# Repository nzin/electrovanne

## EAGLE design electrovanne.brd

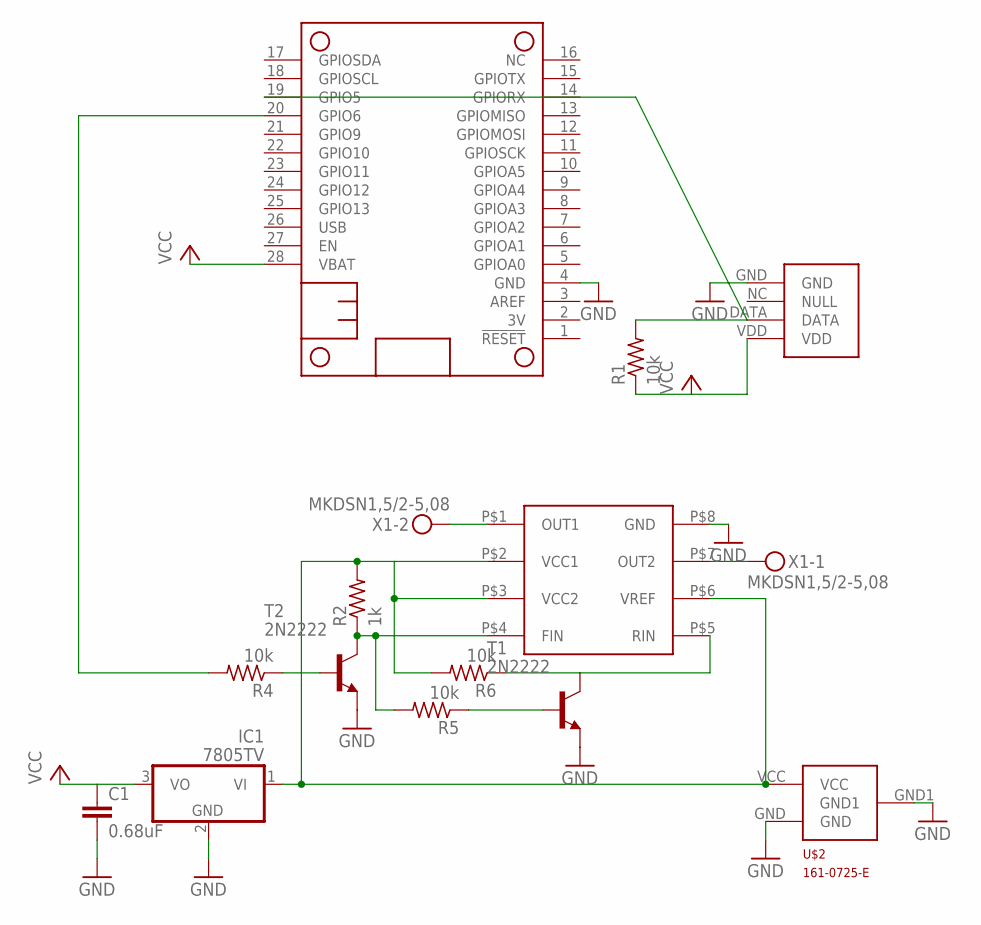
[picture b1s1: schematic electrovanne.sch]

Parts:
C1: 0.68uF; 0603-CAP
IC1: 7805TV; TO220V
MS1: FEATHERWING_NODIM; FEATHERWING_DIM
R1, R4, R5, R6: 10k; R0603
R2: 1k; R0603
T1, T2: 2N2222; TO18
U$1: DHT22
U$2: 161-0725-E
U$4: 755-BD6211F-E2; 755-BD6211F-E2_DIM
X1: MKDSN1,5/2-5,08

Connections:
GND: C1.2, IC1.2 (GND), MS1.4 (GND), T1.1 (E), T2.1 (E), U$1.GND, U$2.GND, U$2.GND1, U$4.P$8 (GND)
unnamed: IC1.1 (VI), R2.2, R6.2, U$2.VCC, U$4.P$2 (VCC1), U$4.P$3 (VCC2), U$4.P$6 (VREF)
unnamed: R5.1, T1.2 (B)
unnamed: MS1.19 (GPIO5), R1.2, U$1.DATA
unnamed: U$4.P$1 (OUT1), X1.2
unnamed: U$4.P$7 (OUT2), X1.1
unnamed: MS1.20 (GPIO6), R4.2
unnamed: R2.1, R5.2, T2.3 (C), U$4.P$4 (FIN)
unnamed: R4.1, T2.2 (B)
unnamed: R6.1, T1.3 (C), U$4.P$5 (RIN)
VCC: C1.1, IC1.3 (VO), MS1.28 (VBAT), R1.1, U$1.VDD

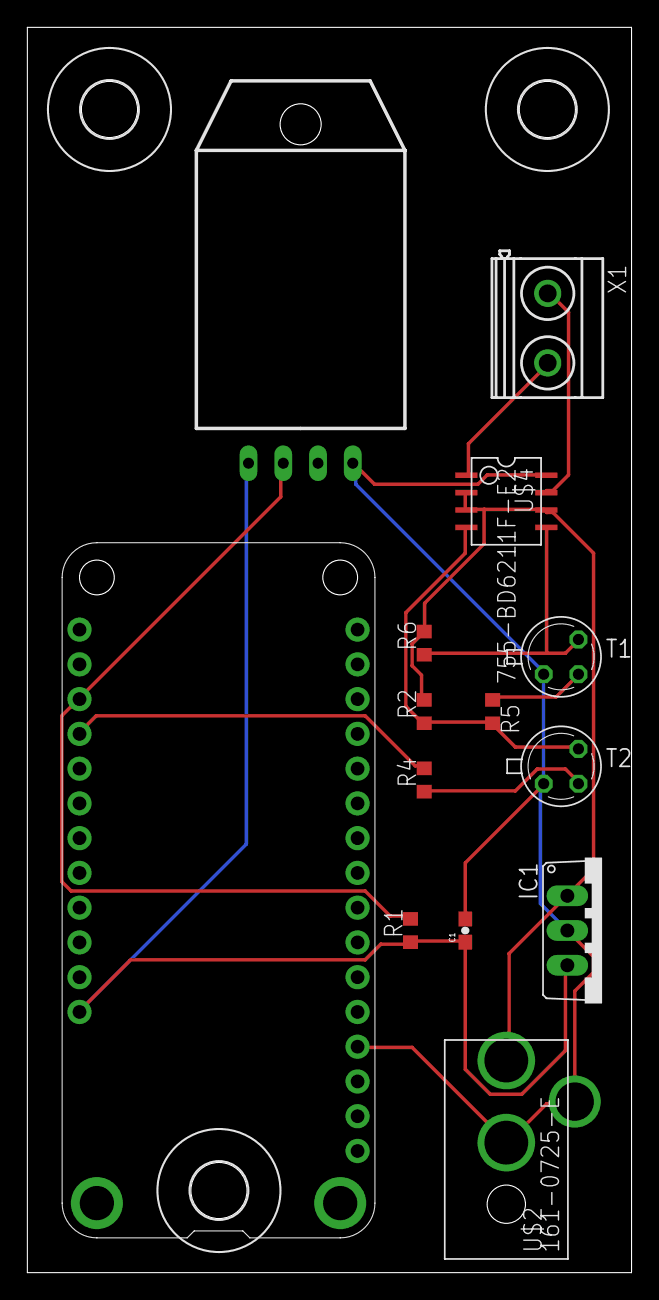
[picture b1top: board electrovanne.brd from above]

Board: 2 copper layers, 44.1 x 91.0 mm, 17 parts (0 on the bottom side), 11 nets.

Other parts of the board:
U$3, U$5, U$6: 4,1

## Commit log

2017-08-28 first draft
2017-08-28 enhanvced version
2017-09-17 2 bugfix: (EN): dont touch to it, + the H-Bridge2 bugfix: (EN): dont touch to it, + the H-Bridge
2017-09-17 add small resistor (recommended by datasheet)
2017-09-17 add holes
2017-10-11 version 3: pb wit the RIN inverter
2017-10-11 add power cord
2017-10-27 add test code
2017-10-29 add freecad model

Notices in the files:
parts and their libraries:
SparkFun-Capacitors: Licensing: Creative Commons ShareAlike 4.0 International - https://creativecommons.org/licenses/by-sa/4.0
